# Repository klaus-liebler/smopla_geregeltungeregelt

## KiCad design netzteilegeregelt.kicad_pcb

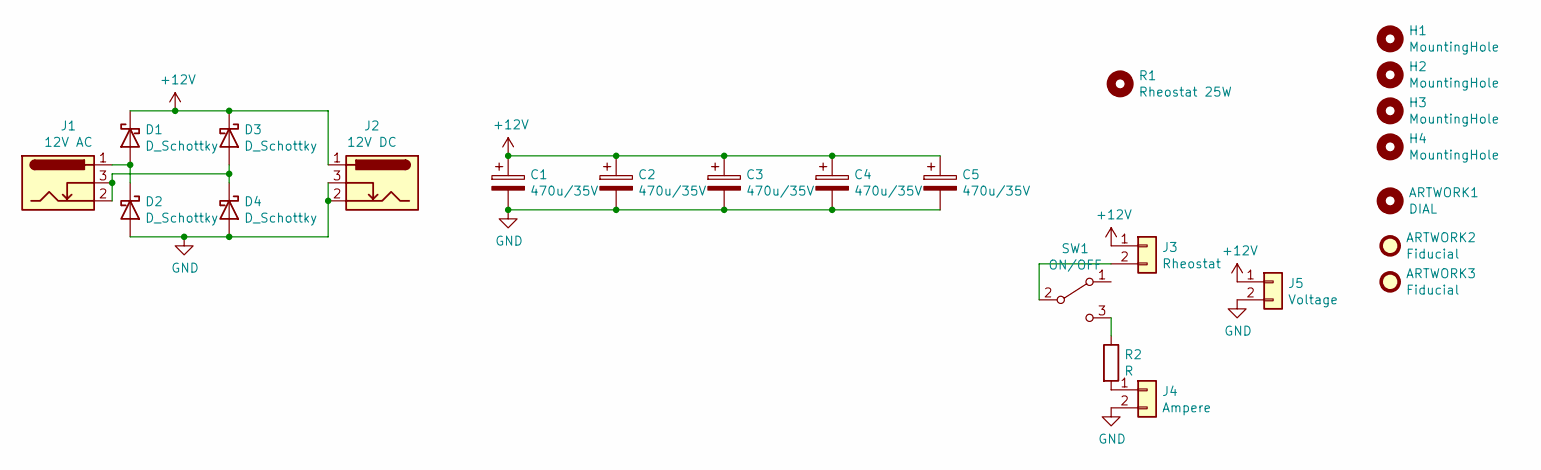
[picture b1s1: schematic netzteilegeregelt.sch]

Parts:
ARTWORK1: DIAL; dial_0_100
ARTWORK2: Fiducial; QR_CODE_smopla_de
ARTWORK3: Fiducial; LOGO_WHS
C1, C2, C3, C4, C5: 470u/35V; CP_Elec_10x10.5
D1, D2, D3, D4: D_Schottky; D_SMC_Handsoldering
H1, H2, H3, H4: MountingHole; MountingHole_3.2mm_M3_DIN965
J1: 12V AC; BarrelJack_Horizontal
J2: 12V DC; BarrelJack_Horizontal
J3: Rheostat; TerminalBlock_bornier-2_P5.08mm
J4: Ampere; TerminalBlock_bornier-2_P5.08mm
J5: Voltage; TerminalBlock_bornier-2_P5.08mm
R1: Rheostat 25W; rheostat_25w
R2: R; Resistor_100W
SW1: ON/OFF; MTS-102

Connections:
+12V: C1.1, C2.1, C3.1, C4.1, C5.1, D1.1 (K), D3.1 (K), J2.1, J3.1, J5.1
GND: C1.2, C2.2, C3.2, C4.2, C5.2, D2.2 (A), D4.2 (A), J2.2, J2.3, J4.2, J5.2
unnamed: D1.2 (A), D2.1 (K), J1.1
unnamed: D3.2 (A), D4.1 (K), J1.2, J1.3
unnamed: J3.2, SW1.2 (B)
unnamed: J4.1, R2.2
unnamed: R2.1, SW1.3 (C)

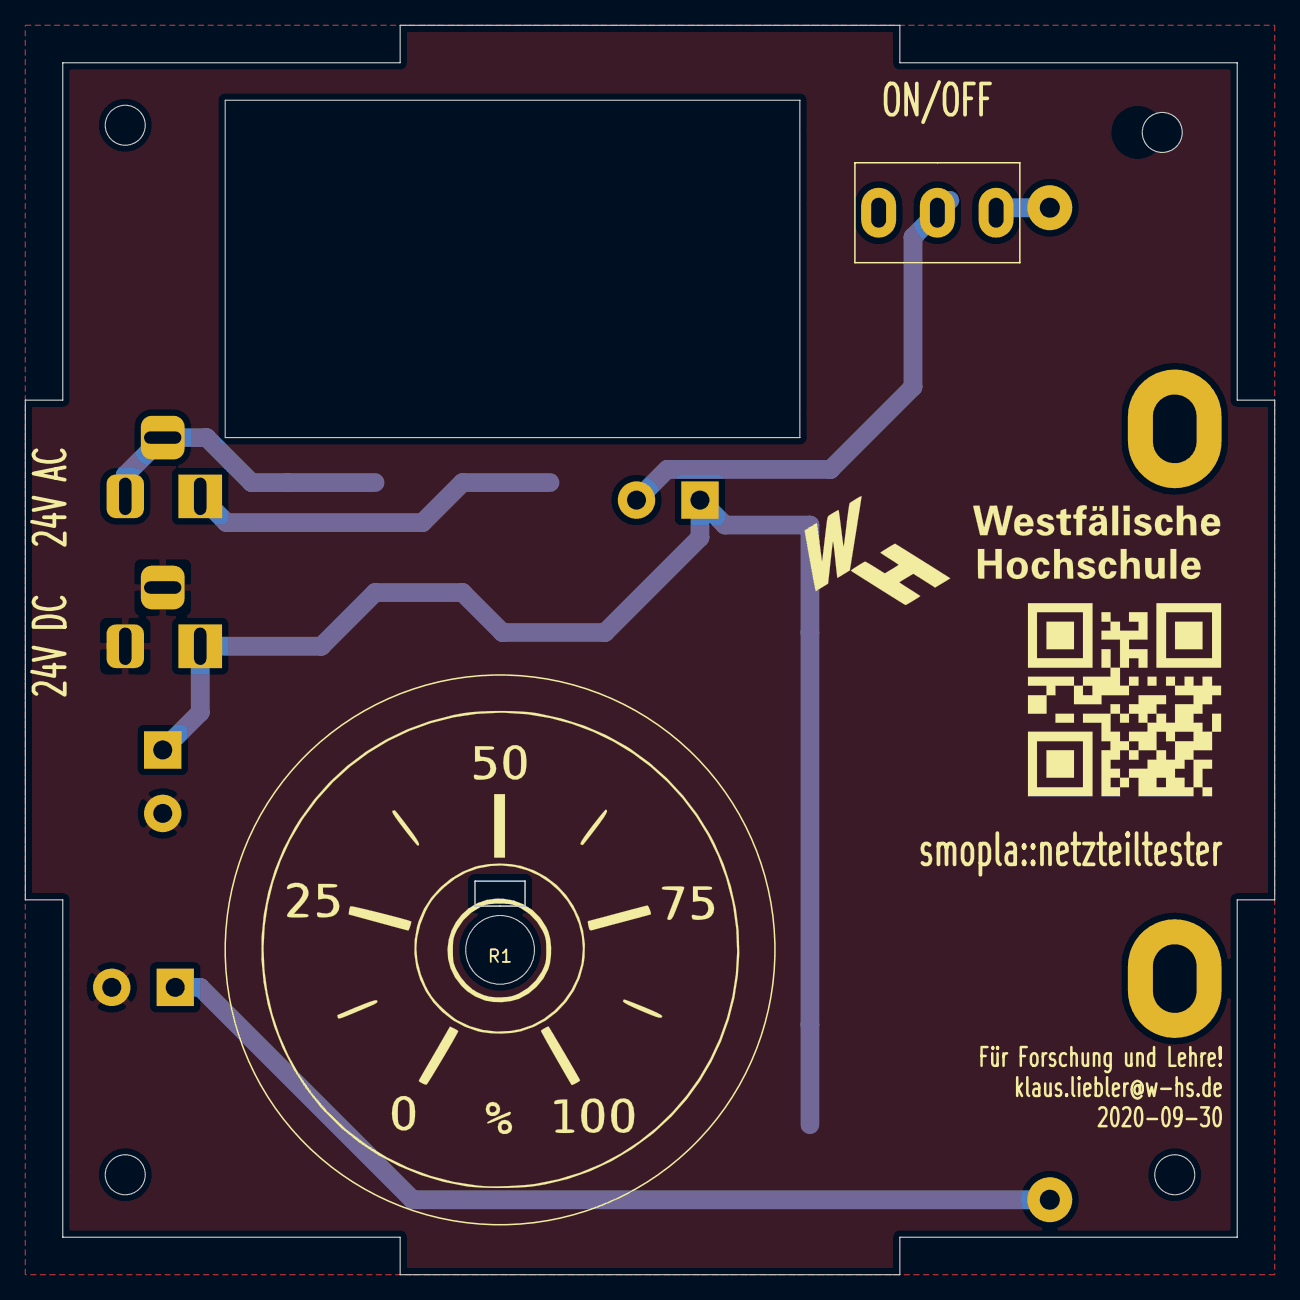
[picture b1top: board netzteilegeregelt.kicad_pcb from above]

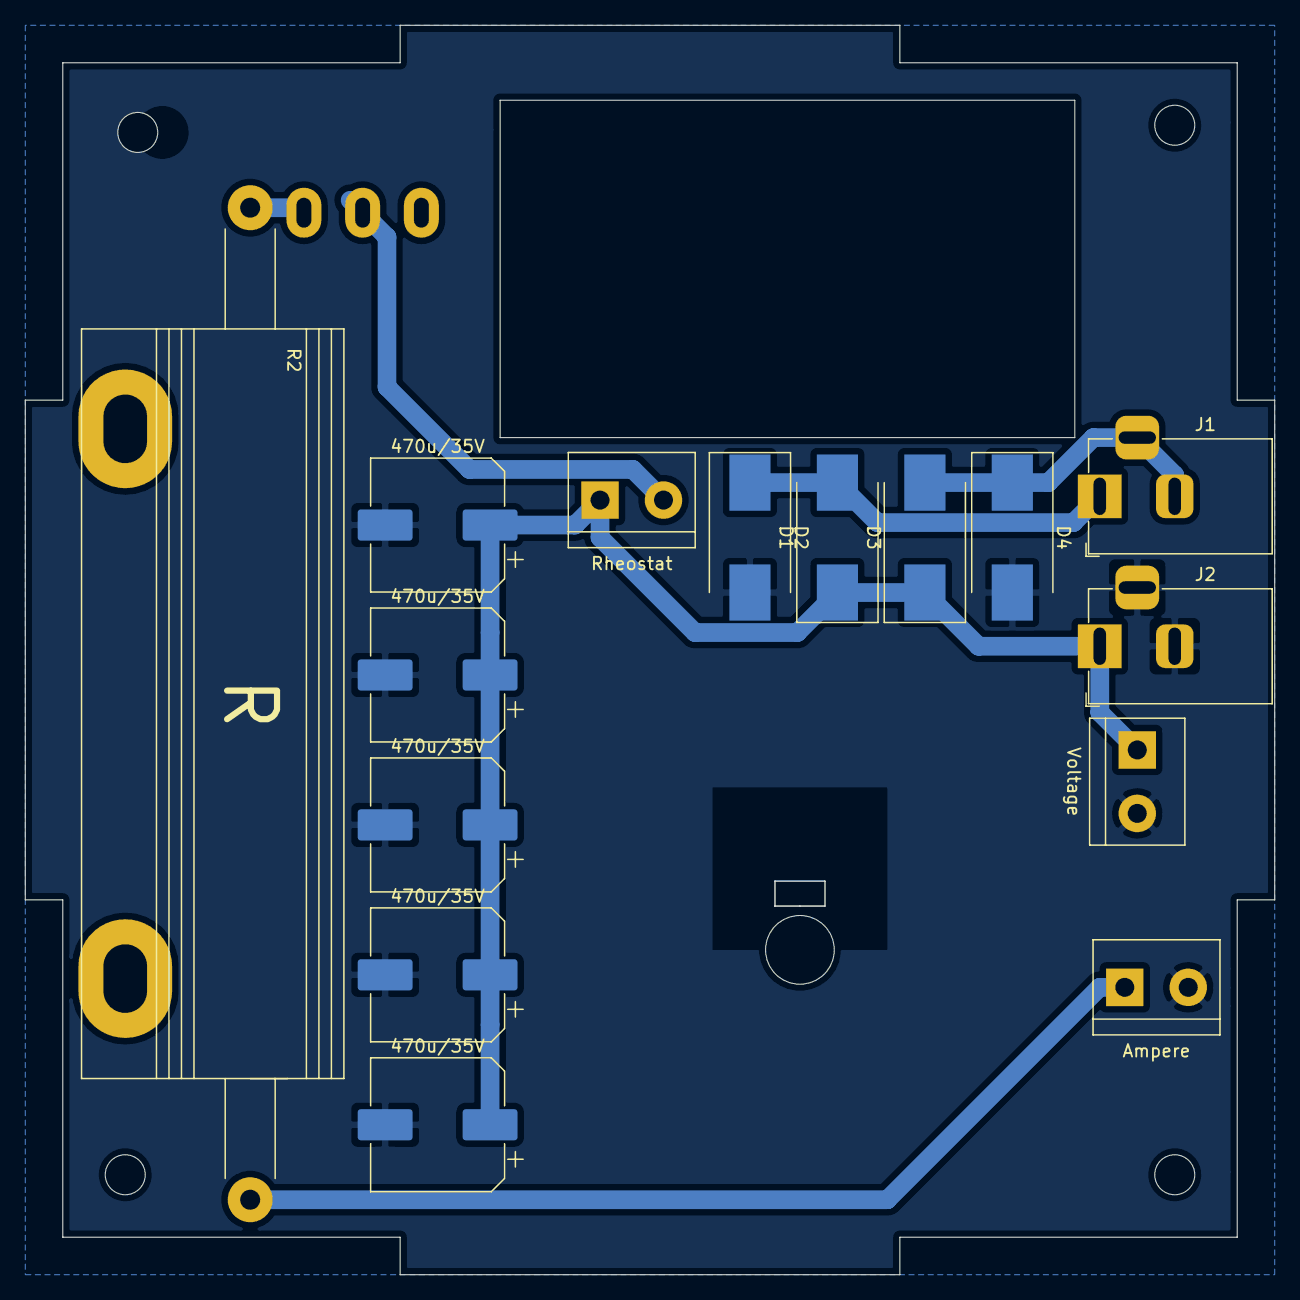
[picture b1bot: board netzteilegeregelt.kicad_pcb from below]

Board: 2 copper layers, 99.9 x 99.9 mm, 24 parts (15 on the bottom side), 7 nets.

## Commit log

2020-11-14 Initial Version
